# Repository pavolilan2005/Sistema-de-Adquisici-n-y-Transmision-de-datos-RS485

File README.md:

# Sistema de adquisición y transmisión de datos

Documentación de los dos firmwares incluidos en esta carpeta. Versiones documentales actuales: STM32 **1.0.1** y gateway ESP32 **1.0.1**.

## Arquitectura

```text
MPU6050 ─I2C1─┐
              ├─ STM32F411 ─ USART1 ─ MAX485 ═ RS485 ═ MAX485 ─ UART2 ─ ESP32 nodo 2
BME680 (pendiente)┘                                              │
                                                                  └─ SPI2 ─ SX1278 ))) LoRa ))) estación nodo 3
```

El STM32 mide el MPU6050 y envía una trama por RS485. El gateway responde el ACK RS485 al recibir una trama válida, la conserva en una cola de una muestra y después la retransmite por LoRa. El gateway espera un ACK de la estación terrena antes de dar por confirmado el salto LoRa. En esta carpeta no está incluido el firmware de la estación nodo 3.

## Firmware STM32F411

Proyecto STM32CubeMX/Keil: `FirmwareSTM32/SistemaAdquisicionDatos/SistemaAdquisicionDatos.ioc` y `MDK-ARM/SistemaAdquisicionDatos.uvprojx`.

### Pines y periféricos

| Función | Pin STM32 |
|---|---|
| I2C1 SCL / SDA | PB6 / PB7 |
| USART1 TX / RX hacia MAX485 | PA9 / PA10 |
| MAX485 DE / `/RE` | PA2 / PA1 |
| LED RX de ACK | PB12 |
| LED TX RS485 | PB13 |
| Heartbeat | PC13 |

I2C1 trabaja a 100 kHz; USART1 trabaja a 115200, 8N1. El MPU6050 está configurado con AD0 a GND (dirección `0x68`), rango de acelerómetro ±2 g y giroscopio ±250 °/s.

**BME680:** este firmware aún no lo inicializa ni lo lee. Los campos de presión, temperatura BME, humedad y gas permanecen en cero en la trama.

### Funcionamiento

- El LED PC13 cambia de estado cada 200 ms como indicador de ejecución.
- Cada segundo se lee el MPU6050, se convierten los valores a mg, mdps y centi-°C, y se transmite la trama.
- El LED TX PB13 se activa durante la transmisión RS485.
- Si llega el ACK correspondiente, RX PB12 se enciende durante 100 ms.
- El timeout de ACK es 300 ms. Si no hay ACK, aumenta `watch_timeout_count`.

## Firmware ESP32 nodo 2

Proyecto ESP-IDF 6.1: `FirmwareESP32`.

### Pines

| Función | GPIO ESP32 |
|---|---:|
| UART2 TX / RX al MAX485 | 17 / 16 |
| MAX485 DE / `/RE` | 33 / 25 |
| LED TX LoRa / LED RX LoRa | 27 / 32 |
| LED integrado | 2 |
| SX1278 SCK / MISO / MOSI | 18 / 19 / 23 |
| SX1278 NSS / RESET / DIO0 | 5 / 4 / 26 |

UART2 también está a 115200, 8N1. En RS485 conecta A con A, B con B y GND común; usa el MAX485 para los dos extremos, no conectes UART directamente entre placas. Revisa terminación y polarización según longitud/topología del bus.

El SX1278 opera a 433 MHz, SF7, BW125 kHz, CR 4/5, CRC habilitado y sync word `0x12`. La banda y el perfil deben coincidir en los otros nodos.

### Tareas FreeRTOS

- `rs485_task`: recibe bytes de UART2, separa líneas por LF y procesa las tramas completas.
- `lora_task`: consume la muestra pendiente, transmite por LoRa y espera el acuse del nodo 3.
- La cola LoRa tiene longitud 1. Si radio está ocupado, una trama nueva sustituye la muestra aún pendiente; aumenta `lora_frames_replaced`.
- La respuesta RS485 se envía inmediatamente después de validar la trama, sin esperar el resultado del enlace LoRa.

## Protocolo

- STM32 → nodo 2: `$D,seq,ax_mg,ay_mg,az_mg,gx_mdps,gy_mdps,gz_mdps,mpu_temp_centiC,pres_Pa,bme_temp_centiC,hum_milliPct,gas_ohm*XX\r\n`
- `XX`: XOR hexadecimal de todos los caracteres entre `$` y `*`, sin incluir delimitadores.
- Nodo 2 → STM32: `$A,seq,OK\r\n`; se envía solo si trama, checksum y secuencia son válidos.
- Nodo 2 → nodo 3: vuelve a enviar la trama válida terminada en CR/LF por LoRa.
- Nodo 3 → nodo 2: ACK aceptado como `$A,seq,OK` o `ACK,seq,OK`, con secuencia igual a la transmitida.

La secuencia es de 8 bits, de 0 a 255, y vuelve a 0 al desbordarse. Los campos BME en cero indican que la lectura aún no está implementada en el firmware STM32; no representan una medición ambiental real.

## Compilar y cargar

### STM32

1. Abre el archivo `.ioc` con STM32CubeMX/CubeIDE para revisar la configuración de periféricos.
2. Abre `MDK-ARM/SistemaAdquisicionDatos.uvprojx` en Keil MDK.
3. Compila el target `SistemaAdquisicionDatos` y programa el STM32F411CEU6 mediante ST-Link.

### ESP32

Desde PowerShell con ESP-IDF 6.1 cargado:

```powershell
cd FirmwareESP32
idf.py set-target esp32
idf.py build
idf.py -p COMx flash monitor
```

Sustituye `COMx` por el puerto del ESP32. El log informa inicio del nodo, recepción de tramas RS485, transmisión LoRa y recepción/timeouts de ACK.

## Versionado

El número de versión de cada fuente está en su comentario inicial. Al modificar código, incrementa el PATCH del firmware correspondiente y actualiza el `project(... VERSION ...)` del CMake de ESP-IDF y esta documentación.

## Archivos de apoyo

- [Mapa de trama, unidades y variables Keil Watch](docs/Protocolo-y-Keil-Watch.md)
- [README del gateway ESP32](FirmwareESP32/README.md)

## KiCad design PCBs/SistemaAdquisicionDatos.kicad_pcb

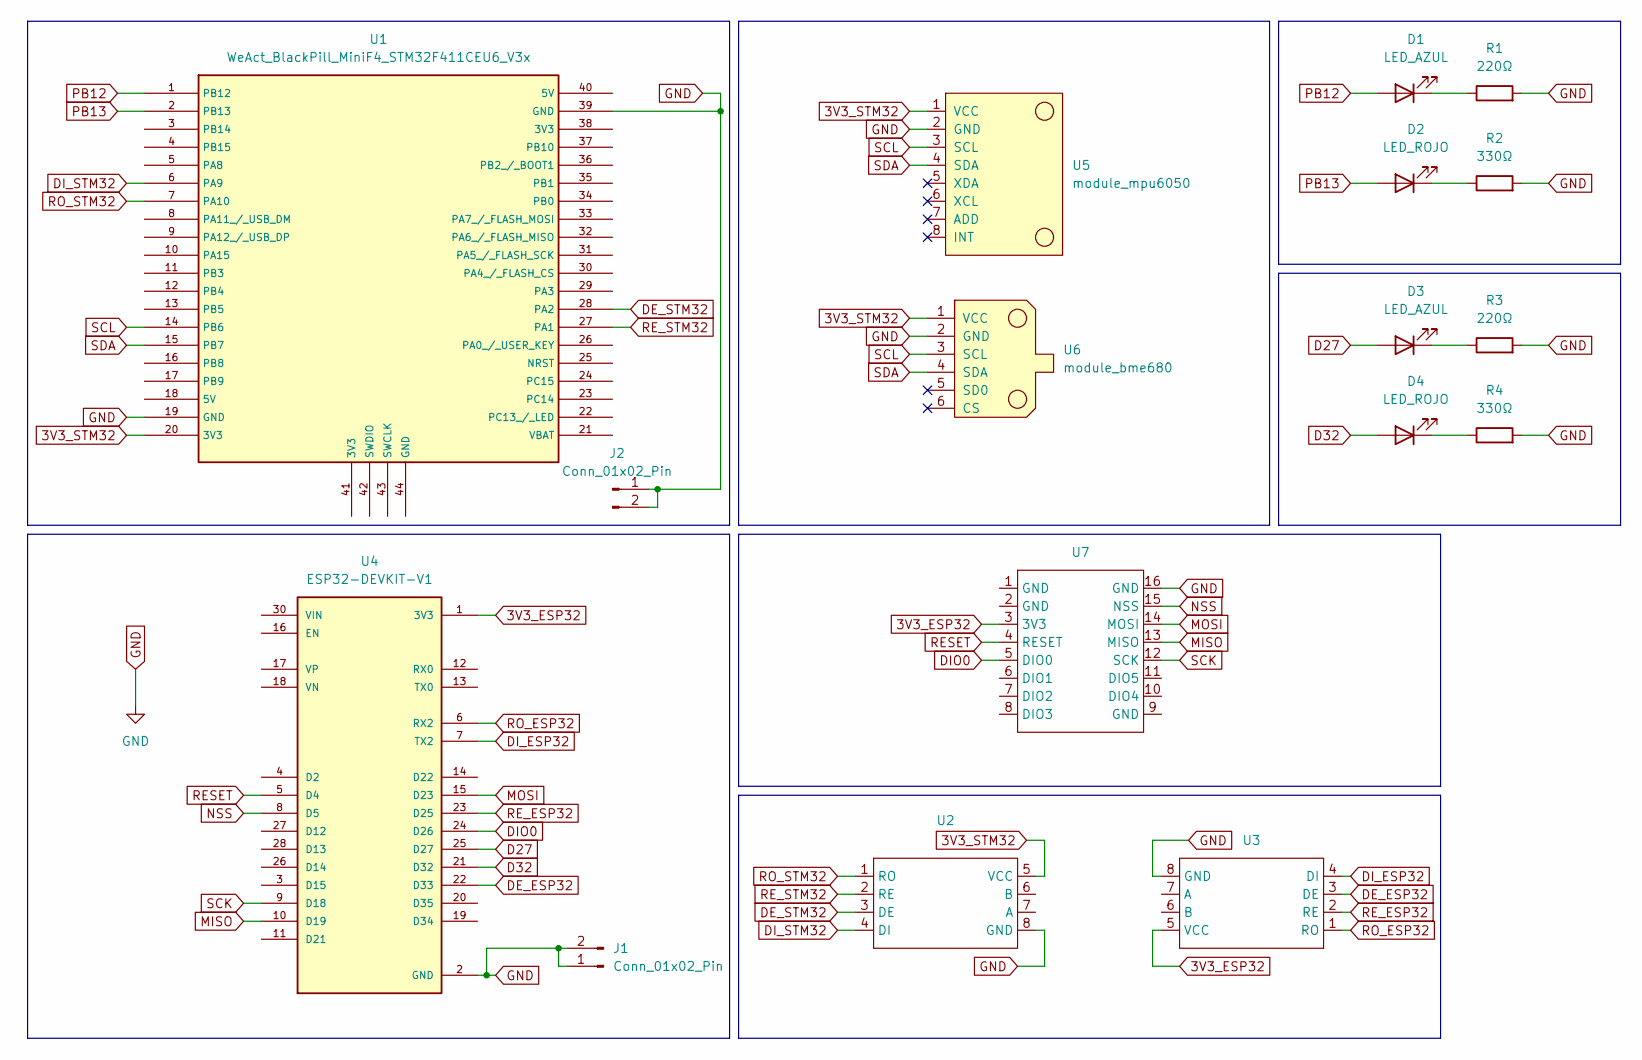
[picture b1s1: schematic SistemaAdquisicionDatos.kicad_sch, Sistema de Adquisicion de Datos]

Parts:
D1, D3: LED_AZUL; LED_D5.0mm
D2, D4: LED_ROJO; LED_D5.0mm
J1, J2: Conn_01x02_Pin; TerminalBlock_Phoenix_MKDS-1,5-2-5.08_1x02_P5.08mm_Horizont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
R1, R3: 220Ω; R_Axial_DIN0207_L6.3mm_D2.5mm_P15.24mm_Horizontal
R2, R4: 330Ω; R_Axial_DIN0207_L6.3mm_D2.5mm_P15.24mm_Horizontal
U1: WeAct_BlackPill_MiniF4_STM32F411CEU6_V3x
U2, U3: MAXRS485
U4: ESP32-DEVKIT-V1; MODULE_ESP32_DEVKIT_V1; PARTREV N/A
U5: module_mpu6050
U6: module_bme680
U7: LoraSX1278

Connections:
3V3_ESP32: U3.5 (VCC), U4.1 (3V3), U7.3 (3V3)
3V3_STM32: U1.20 (3V3), U2.5 (VCC), U5.1 (VCC), U6.1 (VCC)
D27: D3.2 (A), U4.25 (D27)
D32: D4.2 (A), U4.21 (D32)
DE_ESP32: U3.3 (DE), U4.22 (D33)
DE_STM32: U1.28 (PA2), U2.3 (DE)
DIO0: U4.24 (D26), U7.5 (DIO0)
DI_ESP32: U3.4 (DI), U4.7 (TX2)
DI_STM32: U1.6 (PA9), U2.4 (DI)
GND: J1.1, J1.2, J2.1, J2.2, R1.2, R2.2, R3.2, R4.2, U1.19 (GND), U1.39 (GND), U2.8 (GND), U3.8 (GND), U4.2 (GND), U4.29 (GND), U5.2 (GND), U6.2 (GND), U7.16 (GND)
MISO: U4.10 (D19), U7.13 (MISO)
MOSI: U4.15 (D23), U7.14 (MOSI)
NSS: U4.8 (D5), U7.15 (NSS)
unnamed: D1.1 (K), R1.1
unnamed: D2.1 (K), R2.1
unnamed: D3.1 (K), R3.1
unnamed: D4.1 (K), R4.1
PB12: D1.2 (A), U1.1 (PB12)
PB13: D2.2 (A), U1.2 (PB13)
RESET: U4.5 (D4), U7.4 (RESET)
RE_ESP32: U3.2 (RE), U4.23 (D25)
RE_STM32: U1.27 (PA1), U2.2 (RE)
RO_ESP32: U3.1 (RO), U4.6 (RX2)
RO_STM32: U1.7 (PA10), U2.1 (RO)
SCK: U4.9 (D18), U7.12 (SCK)
SCL: U1.14 (PB6), U5.3 (SCL), U6.3 (SCL)
SDA: U1.15 (PB7), U5.4 (SDA), U6.4 (SDA)

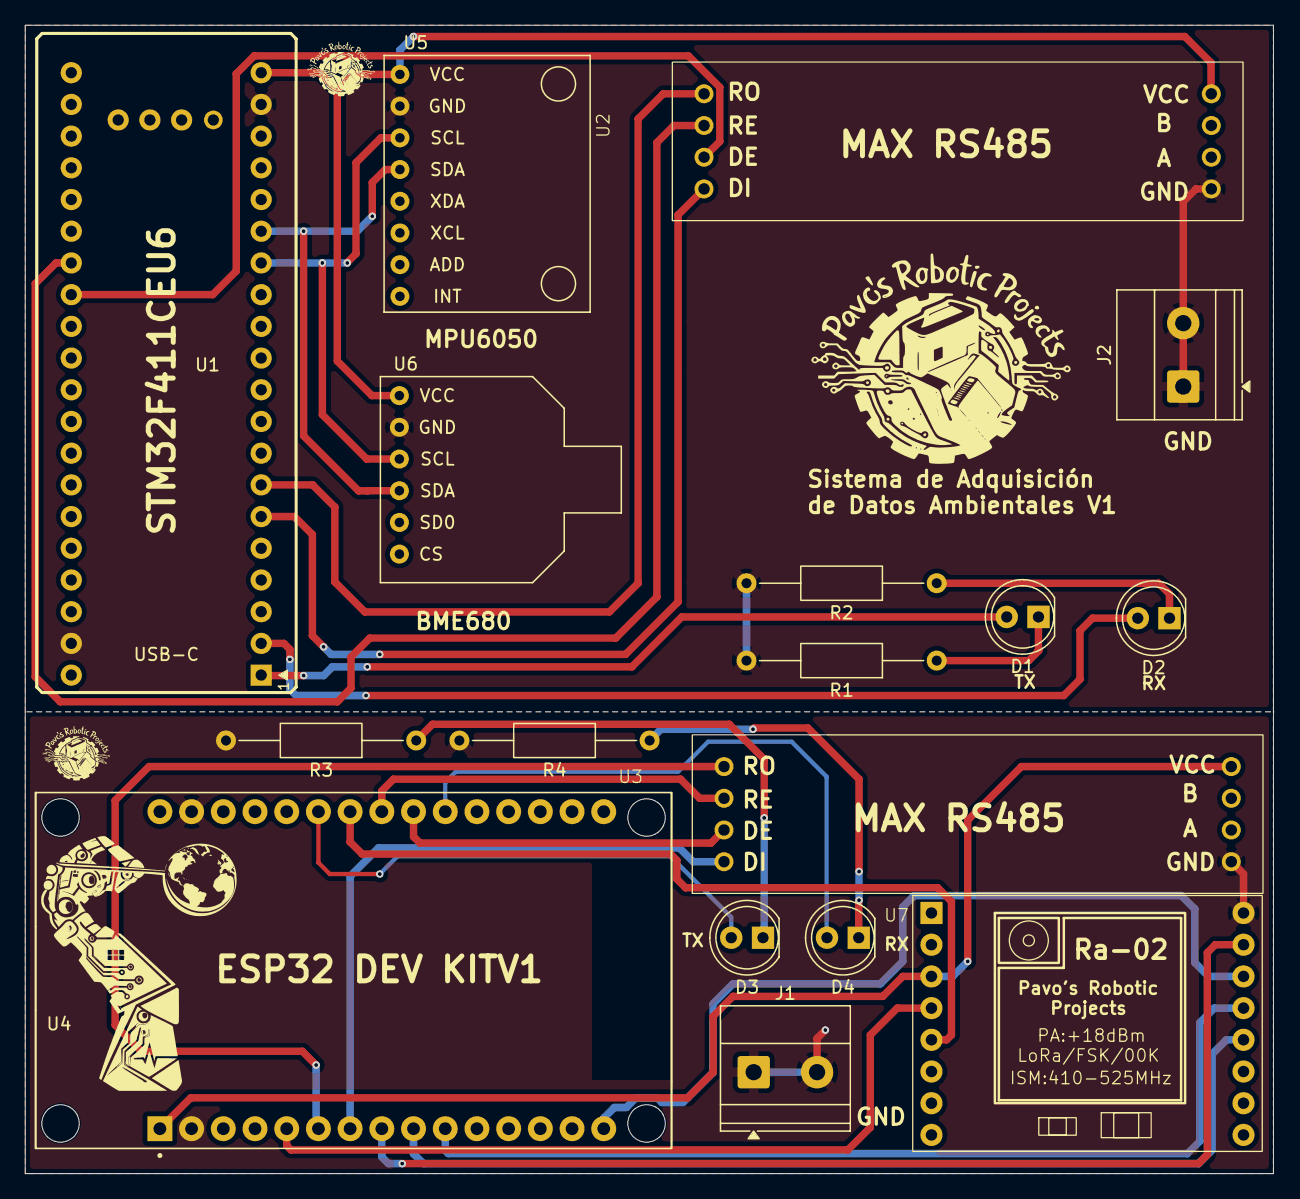
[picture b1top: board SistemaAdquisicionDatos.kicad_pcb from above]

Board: 2 copper layers, 100.0 x 92.0 mm, 17 parts (0 on the bottom side), 27 nets.

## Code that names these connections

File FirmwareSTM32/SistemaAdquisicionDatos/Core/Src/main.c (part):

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void SystemClock_Config(void);
/** Configura DE/RE y LEDs como salidas digitales. */
static void MX_GPIO_Init(void);
/** Configura I2C1 en PB6/PB7 a 100 kHz para los sensores. */
static void MX_I2C1_Init(void);
/** Configura USART1 en PA9/PA10 a 115200 8N1 para el MAX485. */
static void MX_USART1_UART_Init(void);

/** Lee registros I2C con un timeout acotado. */
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    }

    /*
     * Apaga PB12 al finalizar el pulso RX.
     * La resta unsigned funciona también al desbordarse HAL_GetTick().
     */
    if (rx_led_active &&
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    Error_Handler();
}

/** Configura I2C1 en PB6/PB7 a 100 kHz para los sensores. */
static void MX_I2C1_Init(void)
{
  hi2c1.Instance = I2C1;
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    Error_Handler();
}

/** Configura USART1 en PA9/PA10 a 115200 8N1 para el MAX485. */
static void MX_USART1_UART_Init(void)
{
  huart1.Instance = USART1;
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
